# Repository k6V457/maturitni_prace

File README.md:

WOIP
completely incomplete repository

GOALS:
- [x] Create this repository
- [ ] Create graduation thesis
  - [ ] Create template in $\LaTeX$
  - [ ] fill in blank spaces
  - [ ] modify template for SPSKA purposes
  - [ ] Write INTRO and theoretical part
  - [ ] start working on practical part

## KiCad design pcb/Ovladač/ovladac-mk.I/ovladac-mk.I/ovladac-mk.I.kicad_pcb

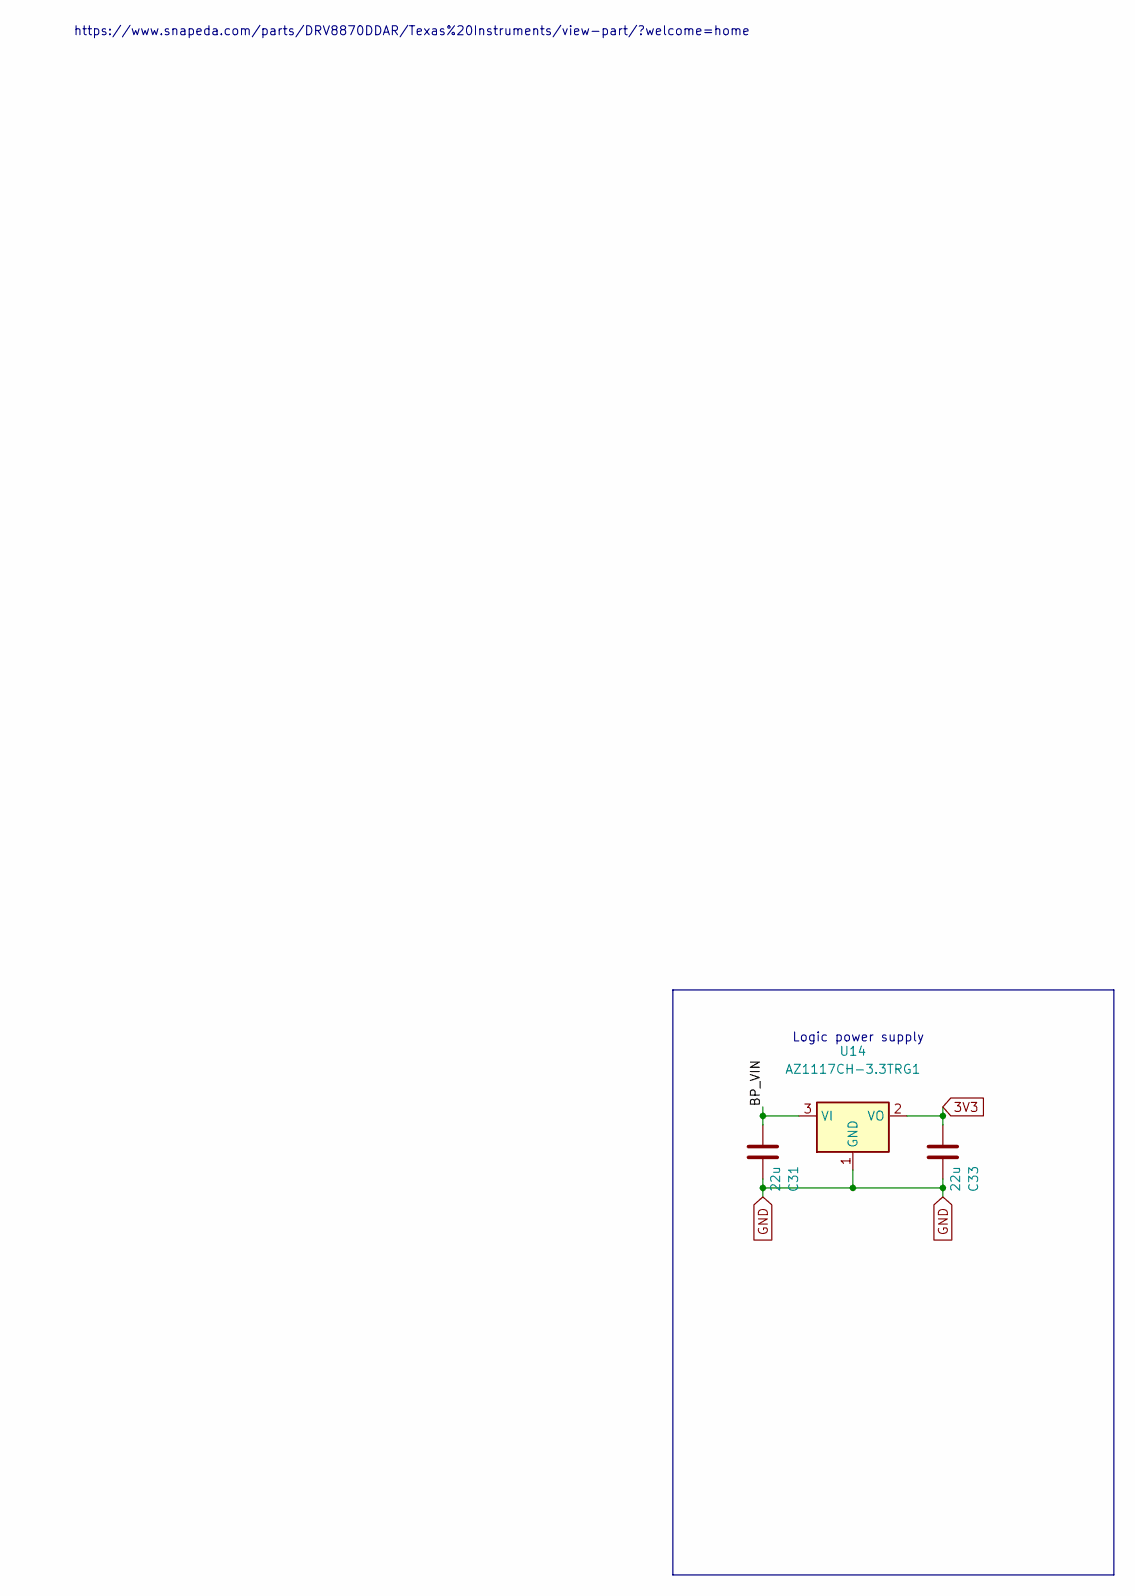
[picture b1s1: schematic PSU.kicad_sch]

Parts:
C31, C33: 22u; C_0603_1608Metric
U14: AZ1117CH-3.3TRG1; SOT-223-3_TabPin2

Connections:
3V3: C33.2, U14.2 (VO); also elsewhere on the board
/PSU/BP_VIN: C31.2, U14.3 (VI); also elsewhere on the board
GND: C31.1, C33.1, U14.1 (GND); also elsewhere on the board

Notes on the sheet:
Logic power supply
https://www.snapeda.com/parts/DRV8870DDAR/Texas%20Instruments/view-part/?welcome=home

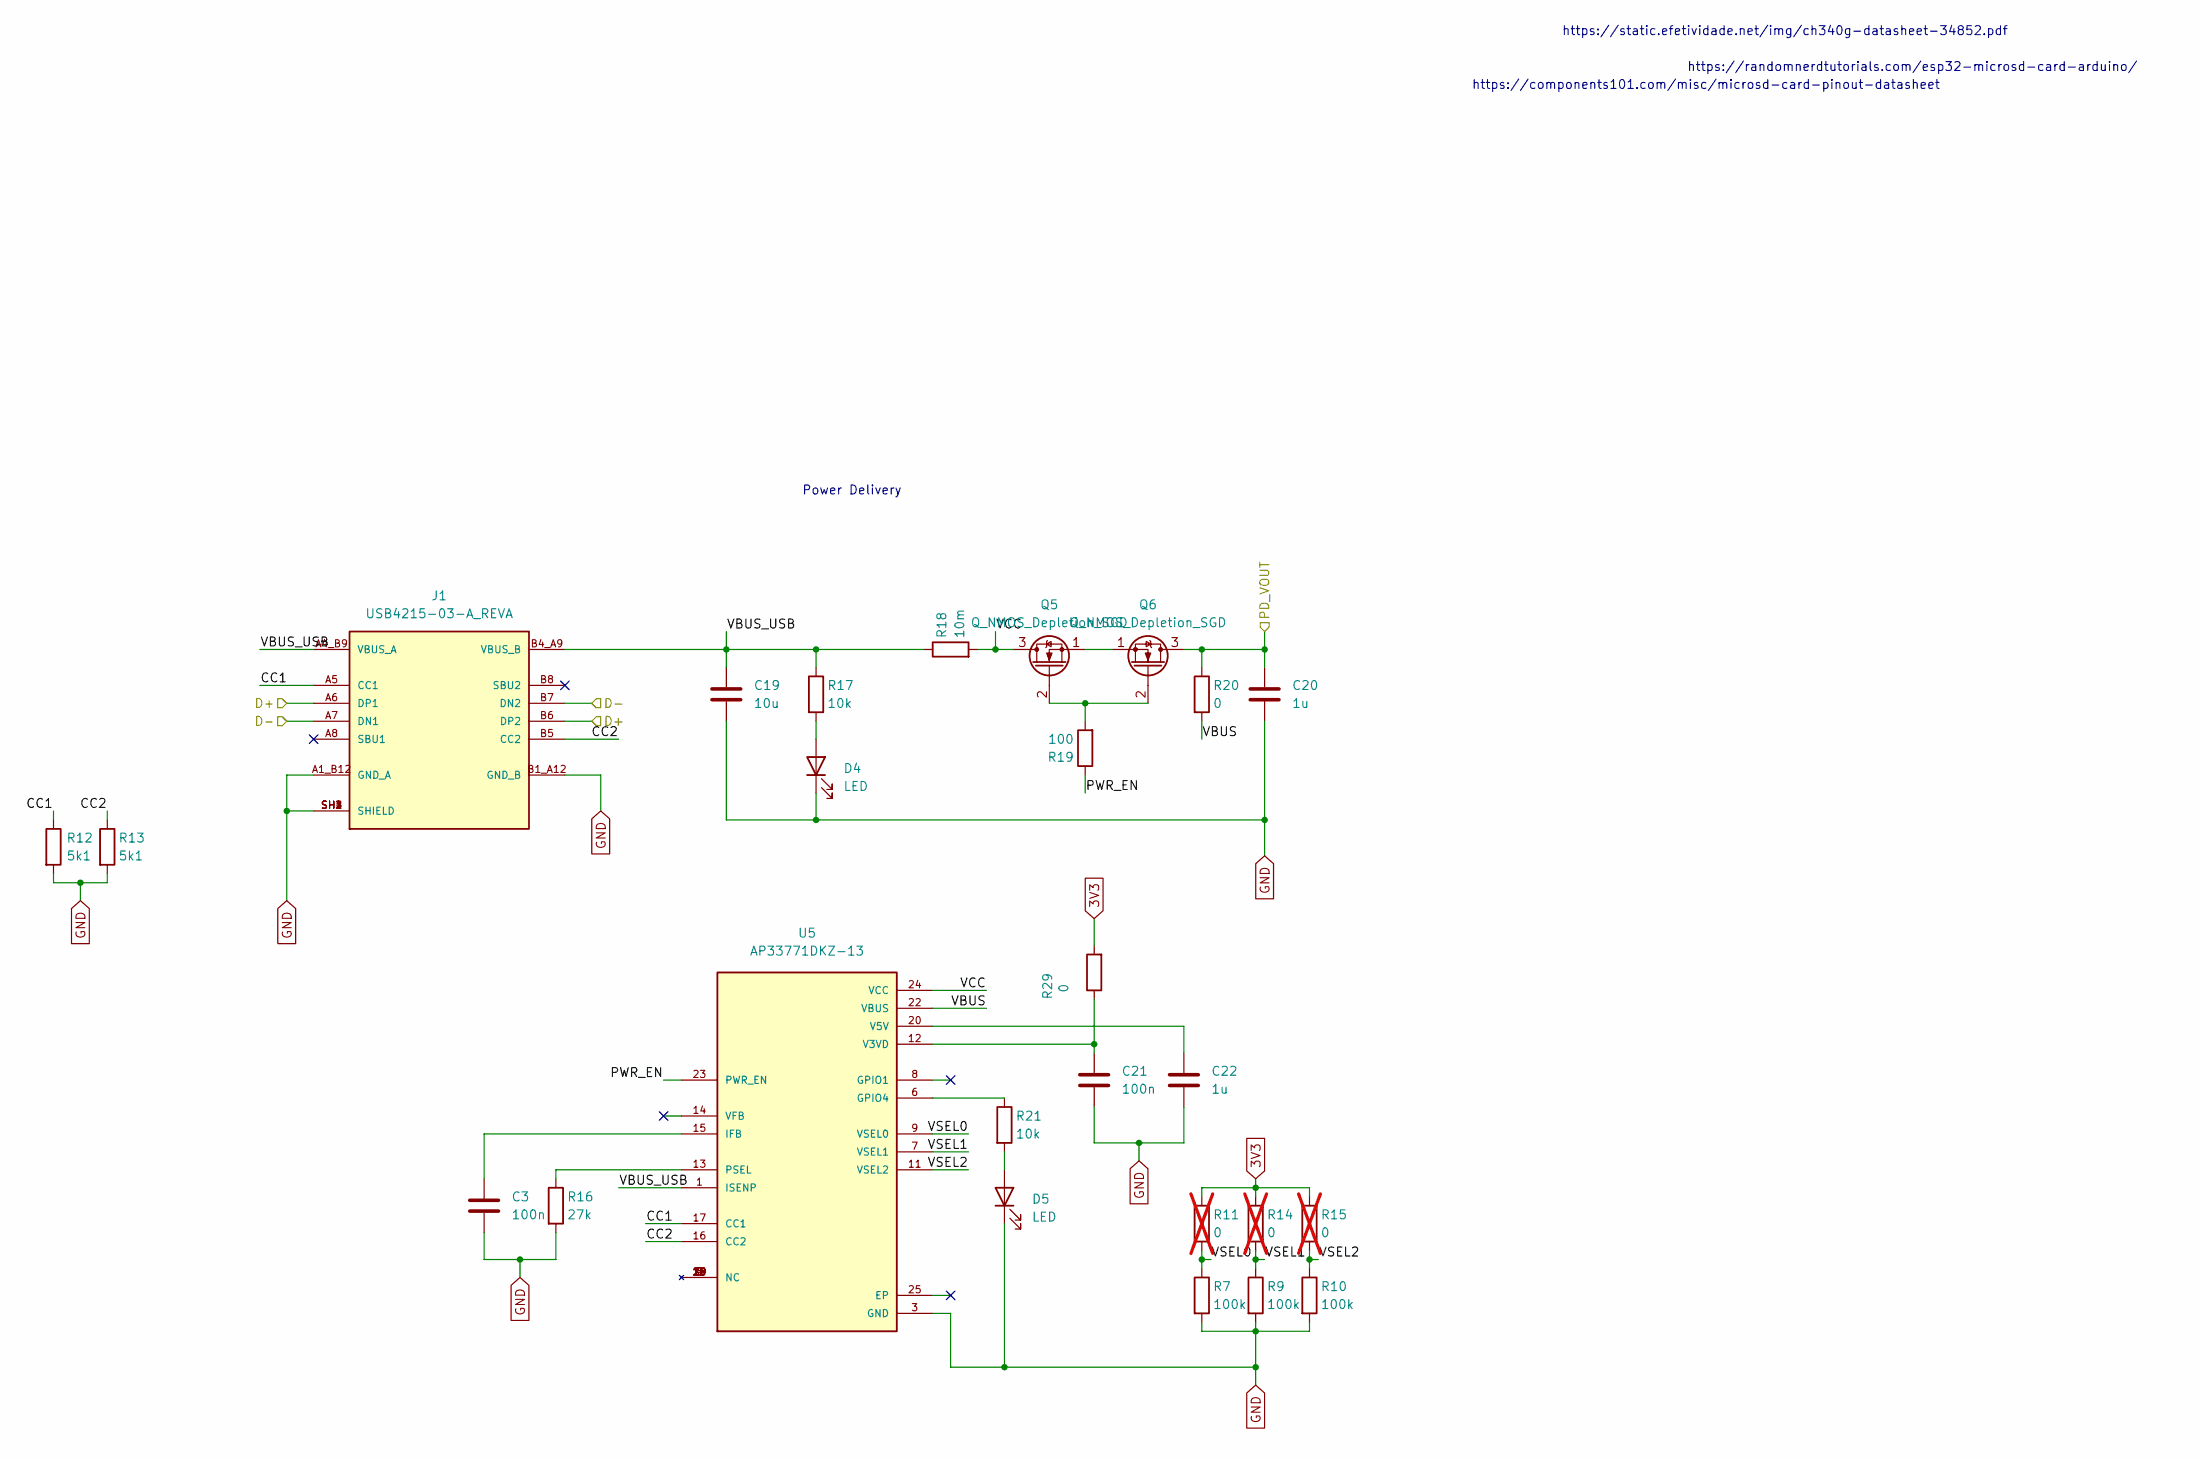
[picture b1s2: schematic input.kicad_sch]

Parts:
C3, C21: 100n; C_0201_0603Metric
C19: 10u; C_0201_0603Metric
C20, C22: 1u; C_0201_0603Metric
D4, D5: LED; LED_0805_2012Metric_Pad1.15x1.40mm_HandSolder
J1: USB4215-03-A_REVA; GCT_USB4215-03-A_REVA; PARTREV A
Q5, Q6: Q_NMOS_Depletion_SGD; SOT-23
R7, R9, R10: 100k; R_0201_0603Metric
R11, R14, R15: 0; R_0201_0603Metric; not fitted
R12, R13: 5k1; R_0201_0603Metric
R16: 27k; R_0805_2012Metric_Pad1.20x1.40mm_HandSolder
R17, R21: 10k; R_0201_0603Metric
R18: 10m; R_0603_1608Metric
R19: 100; R_0201_0603Metric
R20, R29: 0; R_0201_0603Metric
U5: AP33771DKZ-13; IC_AP33771DKZ-13; PARTREV 5-2; DigiKey_Part_Number 31-AP33771DKZ-13TR-ND

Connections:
3V3: R11.1, R14.1, R15.1, R29.2; also elsewhere on the board
/ESP32/IO19: J1.A7 (DN1), J1.B7 (DN2); also elsewhere on the board
/ESP32/IO20: J1.A6 (DP1), J1.B6 (DP2); also elsewhere on the board
/Input/CC1: J1.A5 (CC1), R12.1, U5.17 (CC1)
/Input/CC2: J1.B5 (CC2), R13.1, U5.16 (CC2)
/Input/PD_VOUT: C20.1, Q6.3 (D), R20.1
/Input/PWR_EN: R19.1, U5.23 (PWR_EN)
/Input/VBUS: R20.2, U5.22 (VBUS)
/Input/VBUS_USB: C19.1, J1.A4_B9 (VBUS_A), J1.B4_A9 (VBUS_B), R17.1, R18.1, U5.1 (ISENP)
/Input/VCC: Q5.3 (D), R18.2, U5.24 (VCC)
/Input/VSEL0: R7.1, R11.2, U5.9 (VSEL0)
/Input/VSEL1: R9.1, R14.2, U5.7 (VSEL1)
/Input/VSEL2: R10.1, R15.2, U5.11 (VSEL2)
GND: C3.2, C19.2, C20.2, C21.2, C22.2, D4.1 (K), D5.1 (K), J1.A1_B12 (GND_A), J1.B1_A12 (GND_B), J1.SH1 (SHIELD), J1.SH2 (SHIELD), J1.SH3 (SHIELD), J1.SH4 (SHIELD), R7.2, R9.2, R10.2, R12.2, R13.2, R16.2, U5.3 (GND); also elsewhere on the board
unnamed: D4.2 (A), R17.2
unnamed: D5.2 (A), R21.2
unnamed: Q5.2 (G), Q6.2 (G), R19.2
unnamed: Q5.1 (S), Q6.1 (S)
unnamed: R21.1, U5.6 (GPIO4)
unnamed: C3.1, U5.15 (IFB)
unnamed: R16.1, U5.13 (PSEL)
unnamed: C21.1, R29.1, U5.12 (V3VD)
unnamed: C22.1, U5.20 (V5V)

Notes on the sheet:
https://components101.com/misc/microsd-card-pinout-datasheet
https://static.efetividade.net/img/ch340g-datasheet-34852.pdf
https://randomnerdtutorials.com/esp32-microsd-card-arduino/
Power Delivery

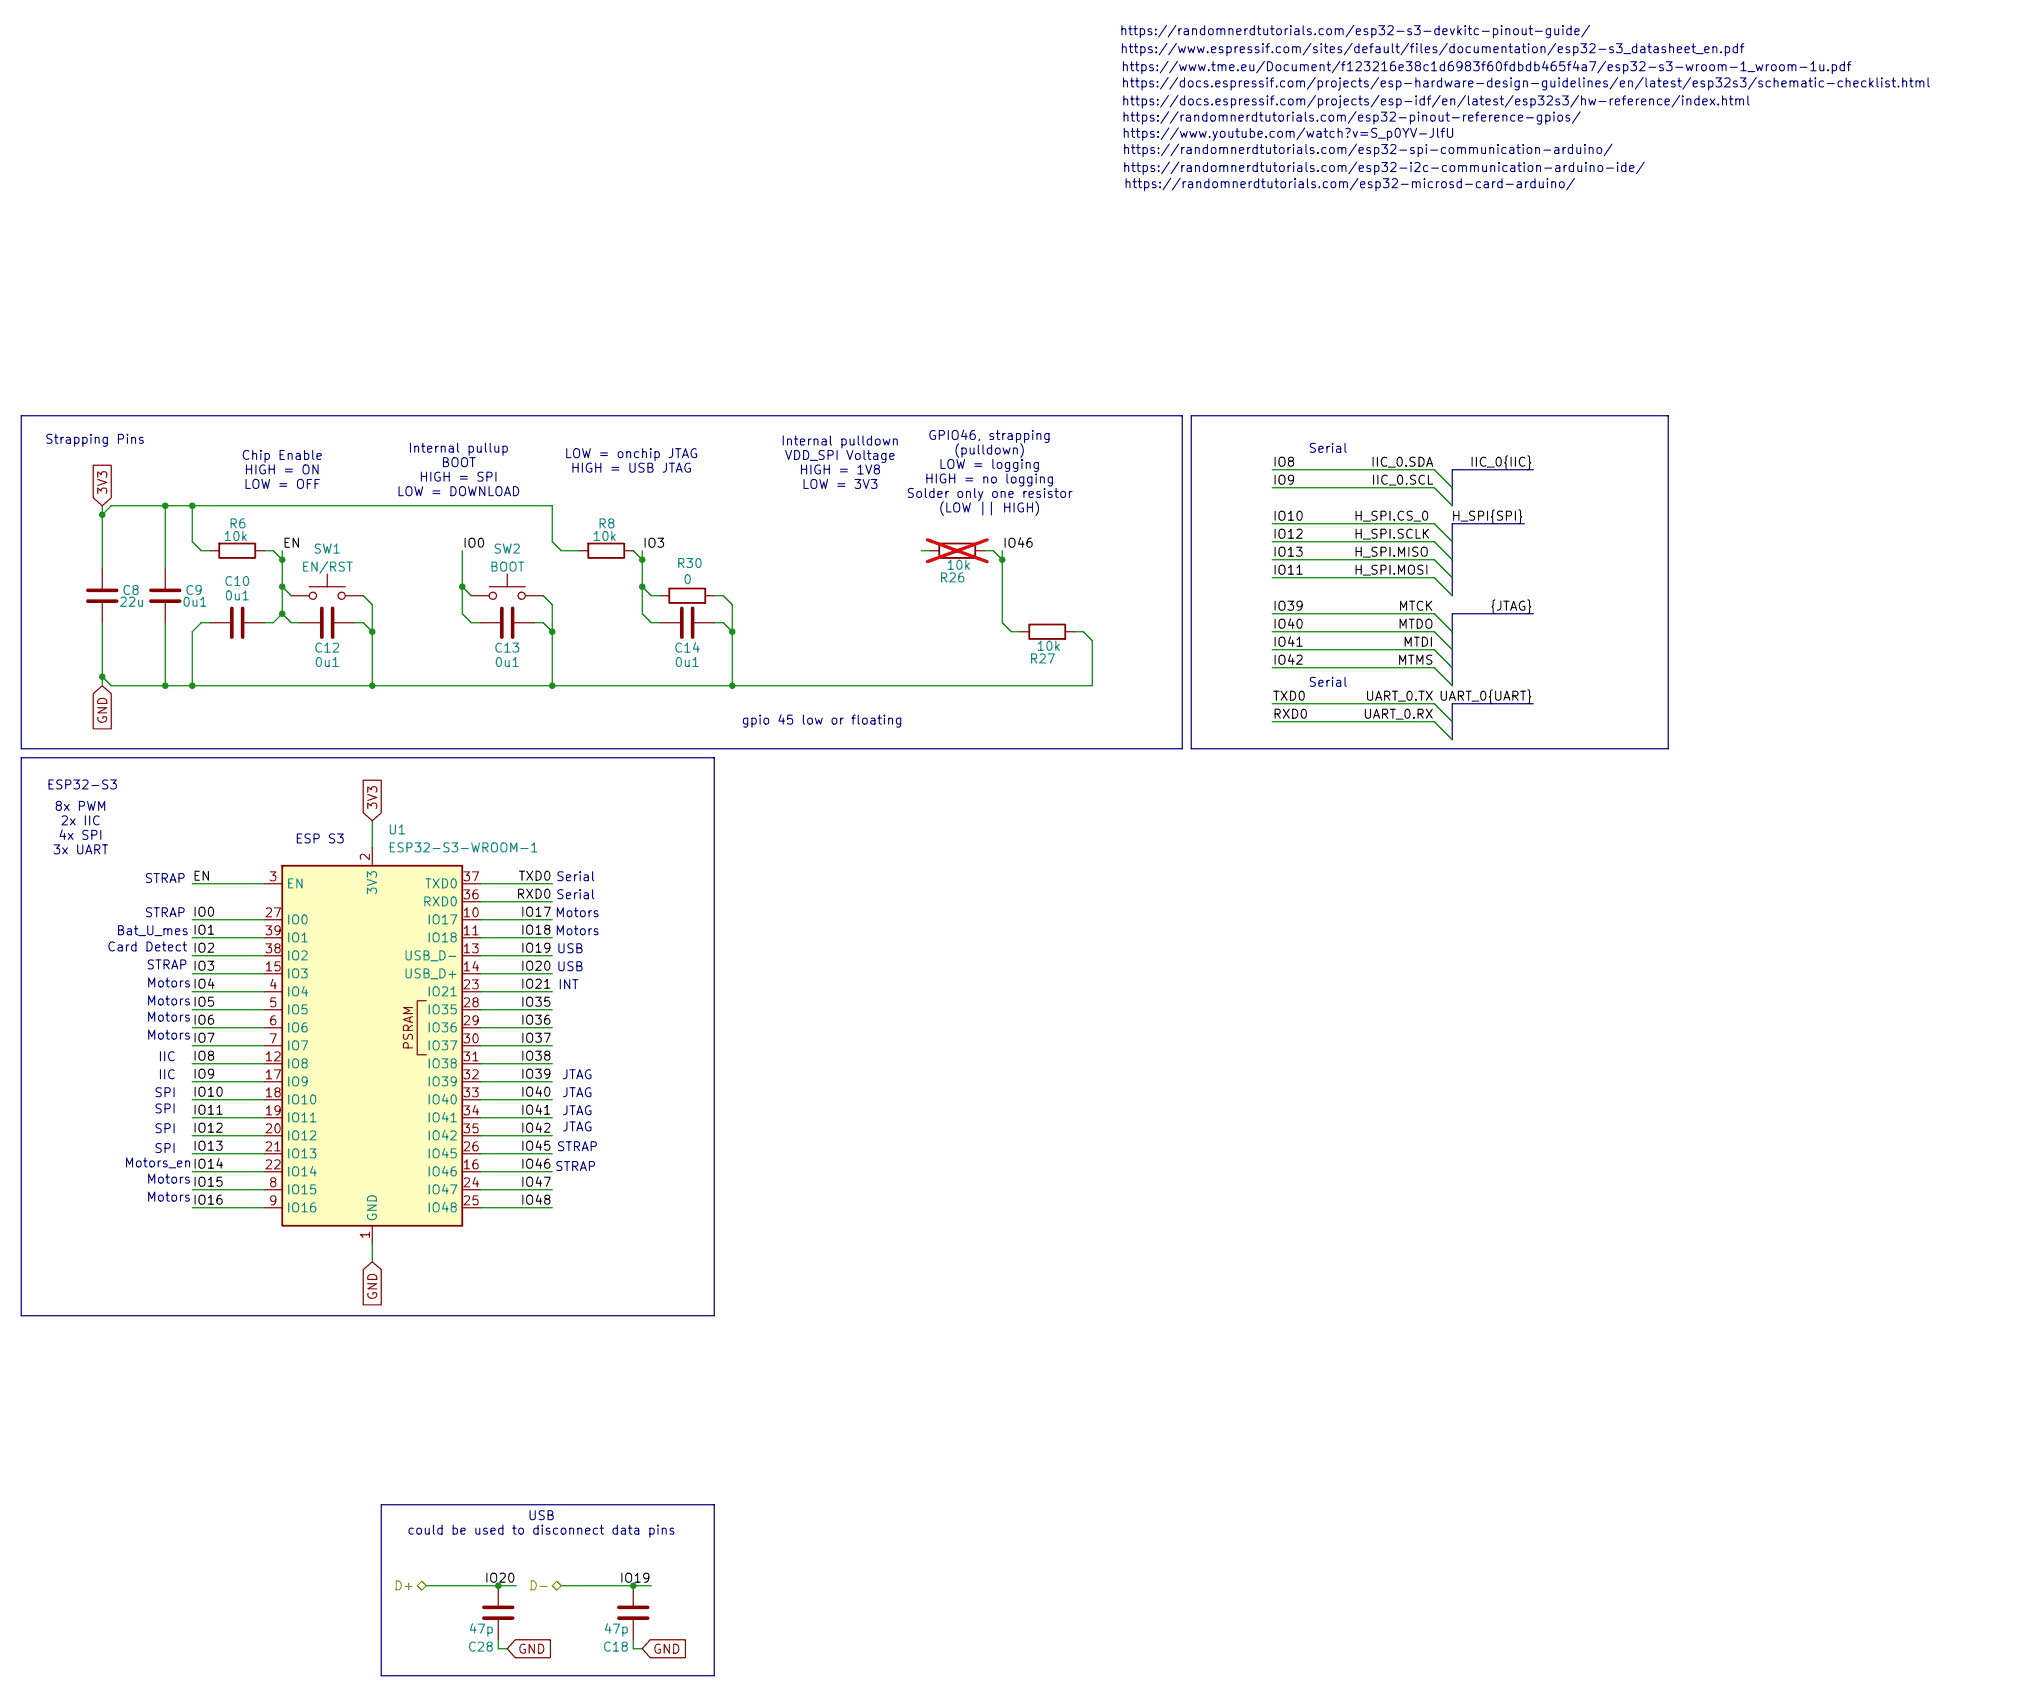
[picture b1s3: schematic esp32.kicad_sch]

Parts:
C8: 22u; C_0402_1005Metric
C9: 0u1; C_0402_1005Metric
C10, C12, C13, C14: 0u1; C_0201_0603Metric
C18, C28: 47p; C_0201_0603Metric
R6, R8, R27: 10k; R_0201_0603Metric
R26: 10k; R_0201_0603Metric; not fitted
R30: 0; R_0201_0603Metric
SW1: EN/RST; SW_TL3305AF160QG
SW2: BOOT; SW_TL3305AF160QG
U1: ESP32-S3-WROOM-1

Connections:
3V3: C8.1, C9.1, R6.2, R8.2, U1.2 (3V3); also elsewhere on the board
/ESP32/EN: C10.1, C12.2, R6.1, SW1.1, U1.3 (EN)
/ESP32/H_SPI.CS_0: U1.18 (IO10)
/ESP32/H_SPI.MISO: U1.21 (IO13)
/ESP32/H_SPI.MOSI: U1.19 (IO11)
/ESP32/H_SPI.SCLK: U1.20 (IO12)
/ESP32/IIC_0.SCL: U1.17 (IO9)
/ESP32/IIC_0.SDA: U1.12 (IO8)
/ESP32/IO0: C13.1, SW2.2, U1.27 (IO0)
/ESP32/IO1: U1.39 (IO1)
/ESP32/IO2: U1.38 (IO2)
/ESP32/IO3: C14.1, R8.1, R30.1, U1.15 (IO3)
/ESP32/IO4: U1.4 (IO4)
/ESP32/IO5: U1.5 (IO5)
/ESP32/IO6: U1.6 (IO6)
/ESP32/IO7: U1.7 (IO7)
/ESP32/IO14: U1.22 (IO14)
/ESP32/IO15: U1.8 (IO15)
/ESP32/IO16: U1.9 (IO16)
/ESP32/IO17: U1.10 (IO17)
/ESP32/IO18: U1.11 (IO18)
/ESP32/IO19: C18.2, U1.13 (USB_D-); also elsewhere on the board
/ESP32/IO20: C28.2, U1.14 (USB_D+); also elsewhere on the board
/ESP32/IO21: U1.23 (IO21)
/ESP32/IO35: U1.28 (IO35)
/ESP32/IO36: U1.29 (IO36)
/ESP32/IO37: U1.30 (IO37)
/ESP32/IO38: U1.31 (IO38)
/ESP32/IO39: U1.32 (IO39)
/ESP32/IO40: U1.33 (IO40)
/ESP32/IO41: U1.34 (IO41)
/ESP32/IO42: U1.35 (IO42)
/ESP32/IO45: U1.26 (IO45); also elsewhere on the board
/ESP32/IO46: R26.2, R27.1, U1.16 (IO46)
/ESP32/IO47: U1.24 (IO47)
/ESP32/IO48: U1.25 (IO48)
/ESP32/RXD0: U1.36 (RXD0)
/ESP32/TXD0: U1.37 (TXD0)
GND: C8.2, C9.2, C10.2, C12.1, C13.2, C14.2, C18.1, C28.1, R27.2, R30.2, SW1.2, SW2.1, U1.1 (GND), U1.40 (GND), U1.41 (GND); also elsewhere on the board

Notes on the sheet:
Motors
8x PWM 2x IIC 4x SPI 3x UART
STRAP
LOW = onchip JTAG HIGH = USB JTAG
https://docs.espressif.com/projects/esp-hardware-design-guidelines/en/latest/esp32s3/schematic-checklist.html
Bat_U_mes
Serial
SPI
https://www.youtube.com/watch?v=S_p0YV-JlfU
ESP32-S3
SPI
JTAG
https://randomnerdtutorials.com/esp32-s3-devkitc-pinout-guide/
USB
https://www.tme.eu/Document/f123216e38c1d6983f60fdbdb465f4a7/esp32-s3-wroom-1_wroom-1u.pdf
ESP S3
USB could be used to disconnect data pins
Card Detect
https://randomnerdtutorials.com/esp32-spi-communication-arduino/
gpio 45 low or floating
Serial
Strapping Pins
Internal pulldown VDD_SPI Voltage HIGH = 1V8 LOW = 3V3
Chip Enable HIGH = ON LOW = OFF
Internal pullup BOOT HIGH = SPI LOW = DOWNLOAD
GPIO46, strapping (pulldown) LOW = logging HIGH = no logging Solder only one resistor (LOW || HIGH)
Motors_en
https://randomnerdtutorials.com/esp32-microsd-card-arduino/
https://www.espressif.com/sites/default/files/documentation/esp32-s3_datasheet_en.pdf
https://docs.espressif.com/projects/esp-idf/en/latest/esp32s3/hw-reference/index.html
IIC
https://randomnerdtutorials.com/esp32-pinout-reference-gpios/
https://randomnerdtutorials.com/esp32-i2c-communication-arduino-ide/
INT
JTAG

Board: 2 copper layers, 49 parts (0 on the bottom side), 30 nets, no tracks yet.

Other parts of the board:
C34, C35: 22u; C_0603_1608Metric
R28: 10k; R_0201_0603Metric
U13: AZ1117CH-5.0TRG1; SOT-223-3_TabPin2

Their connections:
5V: C35.2, U13.2 (VO)
/ESP32/IO45: R28.1; also elsewhere on the board
/PSU/BP_VIN: C34.2, U13.3 (VI); also elsewhere on the board
GND: C34.1, C35.1, R28.2, U13.1 (GND); also elsewhere on the board

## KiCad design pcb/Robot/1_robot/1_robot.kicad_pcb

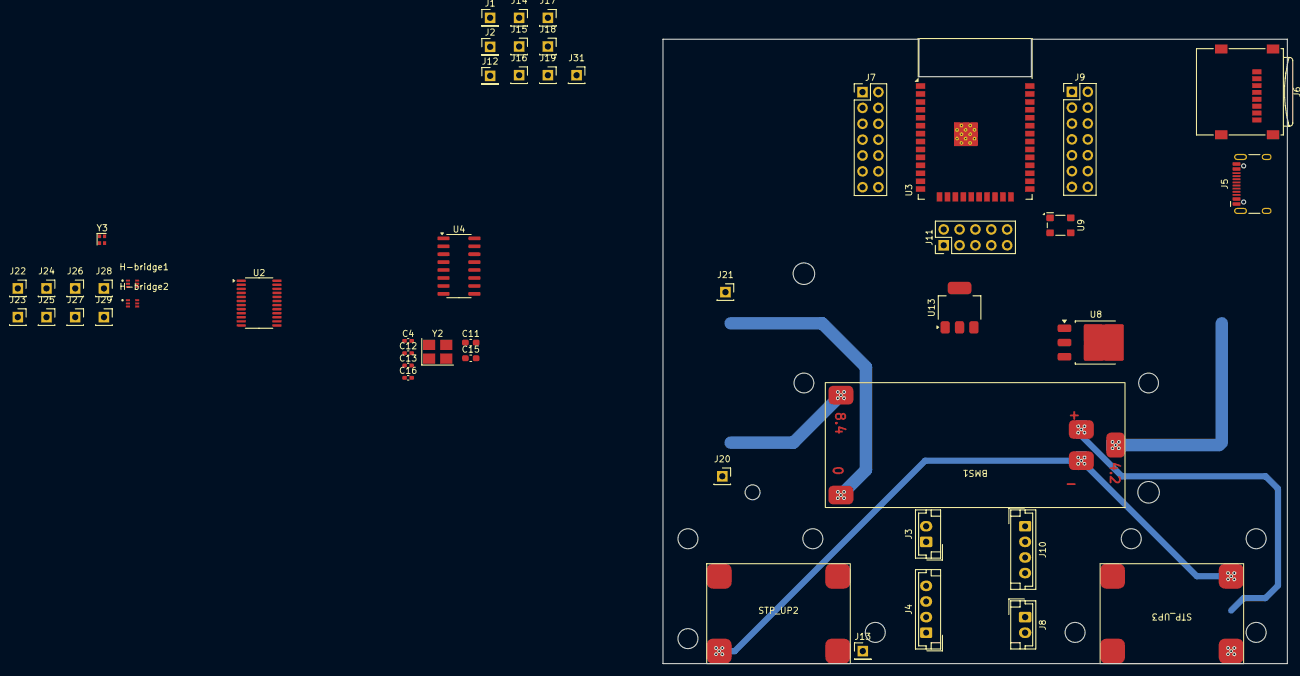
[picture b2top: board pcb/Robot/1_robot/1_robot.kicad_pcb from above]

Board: 2 copper layers, 100.0 x 100.0 mm, 50 parts (1 on the bottom side), 47 nets.

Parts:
BMS1: 2S 20A; BMS
BT1: 1048P; BAT_1048P
C4, C12, C13, C16: C; C_0402_1005Metric_Pad0.74x0.62mm_HandSolder
C11, C15: C; C_0603_1608Metric_Pad1.08x0.95mm_HandSolder
H-bridge1, H-bridge2: SOT50P160X60-6N
J1, J2, J12, J13: Conn_01x01_Socket; PinHeader_1x01_P2.54mm_Vertical
J3, J8: Conn_01x02_Pin; JST_EH_B2B-EH-A_1x02_P2.50mm_Vertical
J4, J10: Conn_01x04_Pin; JST_EH_B4B-EH-A_1x04_P2.50mm_Vertical
J5: USB_C_Receptacle_USB2.0_16P; USB_C_Receptacle_HCTL_HC-TYPE-C-16P-01A
J6: Micro_SD_Card_Det1; microSD_HC_Wuerth_693072010801
J7, J9: Conn_01x14_Pin; PinHeader_2x07_P2.54mm_Vertical
J11: Conn_01x10_Pin; PinHeader_2x05_P2.54mm_Vertical
J14, J15, J16, J17, J18, J19, J20, J21, J22, J23, J24, J25, J26, J27, J28, J29, J31: Conn_01x01_Socket; PinSocket_1x01_P2.54mm_Vertical
STP_UP2, STP_UP3: H-bridge_SX1308 2A
U2: TCA9548APWR; TSSOP-24_4.4x7.8mm_P0.65mm
U3: ESP32-WROOM-32E; ESP32-WROOM-32D
U4: CH340G; SOIC-16_3.9x9.9mm_P1.27mm
U8: LD39150DT33; TO-252-3_TabPin2
U9: GP2S700HCP; Sharp_GP2S700HCP
U13: LD1117S50TR_SOT223; SOT-223-3_TabPin2
Y2: Crystal_GND24; Oscillator_SMD_Abracon_ASE-4Pin_3.2x2.5mm_HandSoldering
Y3: Crystal; Oscillator_SMD_Abracon_ASCO-4Pin_1.6x1.2mm

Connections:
3V3: C11.1, C12.1, C15.1, C16.1, J3.2, J6.4 (VDD), J7.2, J8.2, J15.1, U2.24 (VCC), U3.2 (VDD), U4.4 (V3), U4.16 (VCC), U8.3 (VO)
/5V: J16.1, U13.2 (VO)
/CS_1: J6.2 (DAT3/CD), J9.10, U3.29 (IO5)
/ESP32/EN: J7.3, U3.3 (EN)
/ESP32/IO0: J9.14, U3.25 (IO0)
/ESP32/IO2: J11.10, U3.24 (IO2)
/ESP32/IO4: J9.13, U3.26 (IO4), U9.4 (A)
/ESP32/IO12: J7.14, U3.14 (IO12)
/ESP32/IO13: J11.2, U3.16 (IO13)
/ESP32/IO14: J7.13, U3.13 (IO14)
/ESP32/IO15: J11.9, U3.23 (IO15)
/ESP32/IO16: J9.12, U3.27 (IO16)
/ESP32/IO17: J9.11, U3.28 (IO17)
/ESP32/IO25: J7.10, J10.1, J28.1, U3.10 (IO25)
/ESP32/IO26: J4.1, J7.11, J26.1, U3.11 (IO26)
/ESP32/IO27: J7.12, J10.2, J29.1, U3.12 (IO27)
/ESP32/IO32: J7.8, U3.8 (IO32), Y3.2
/ESP32/IO33: J7.9, U3.9 (IO33), Y3.1
/ESP32/IO34: J4.2, J7.6, J27.1, U3.6 (IO34)
/ESP32/IO35: J7.7, U3.7 (IO35)
/ESP32/RXD0: J9.5, U3.34 (RXD0/IO3)
/ESP32/SDI: J9.3, U3.36 (IO22)
/ESP32/SDO: J9.6, U3.33 (IO21)
/ESP32/Sensor_VN: J7.5, U3.5 (SENSOR_VN)
/ESP32/Sensor_VP: J7.4, U3.4 (SENSOR_VP)
/ESP32/TXD0: J9.4, U3.35 (TXD0/IO1)
/GND: BMS1.5 (OUT_GND), C4.2, C11.2, C12.2, C13.2, C15.2, C16.2, J4.3, J5.A1 (GND), J5.A12 (GND), J5.B1 (GND), J5.B12 (GND), J5.S1 (SHIELD), J6.6 (VSS), J7.1, J9.1, J10.3, J11.1, J14.1, J17.1, J18.1, STP_UP2.2 (GND_IN), STP_UP3.2 (GND_IN), U2.12 (GND), U3.1 (GND), U3.15 (GND), U3.38 (GND), U3.39 (GND), U4.1 (GND), U8.2 (GND), U9.3 (K), U13.1 (GND), Y2.2, Y2.4
/H-Bridge/+12_1: J1.1, STP_UP3.3 (VOUT)
/H-Bridge/+12_2: J12.1, STP_UP2.3 (VOUT)
/H-Bridge/GND_12_1: J2.1, STP_UP3.4 (GND_OUT)
/H-Bridge/GND_12_2: J13.1, STP_UP2.4 (GND_OUT)
/Input/D+: J5.A6 (D+), J5.B6 (D+)
/Input/D-: J5.A7 (D-), J5.B7 (D-)
/Input/VBUS_USB: J5.A4 (VBUS), J5.A9 (VBUS), J5.B4 (VBUS), J5.B9 (VBUS)
/MISO: J6.7 (DAT0), J9.8, U3.31 (IO19)
/MOSI: J6.3 (CMD), J9.2, U3.37 (IO23)
/PSU/BP_VIN: BMS1.4 (OUT_8.4V), J19.1, U8.1 (VI), U9.2, U13.3 (VI)
/SCLK: J6.5 (CLK), J9.9, U3.30 (IO18)
unnamed: BMS1.3 (0V), BT1.N1, J21.1
unnamed: BMS1.2 (4.2V), BT1.N2, BT1.P1, J31.1
unnamed: BMS1.1 (8.4V), BT1.P2, J20.1
unnamed: J8.1, J22.1
unnamed: J10.4, J24.1
unnamed: J3.1, J23.1
unnamed: J4.4, J25.1
unnamed: C4.1, U4.7 (XI), Y2.1
unnamed: C13.1, U4.8 (XO), Y2.3

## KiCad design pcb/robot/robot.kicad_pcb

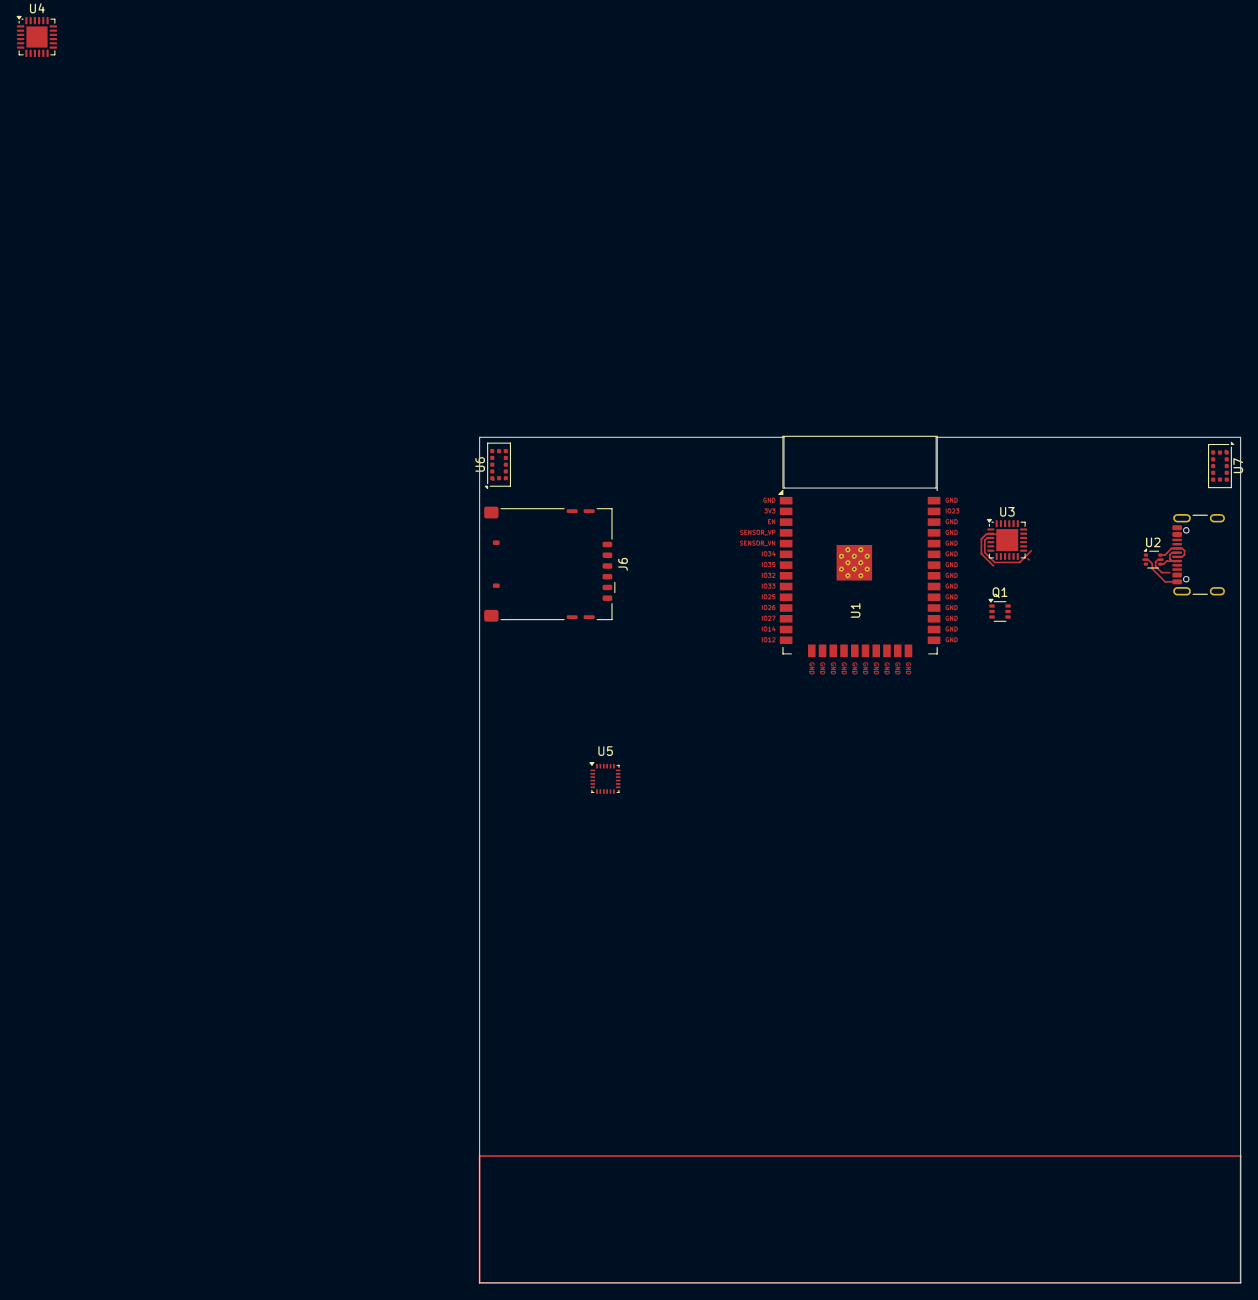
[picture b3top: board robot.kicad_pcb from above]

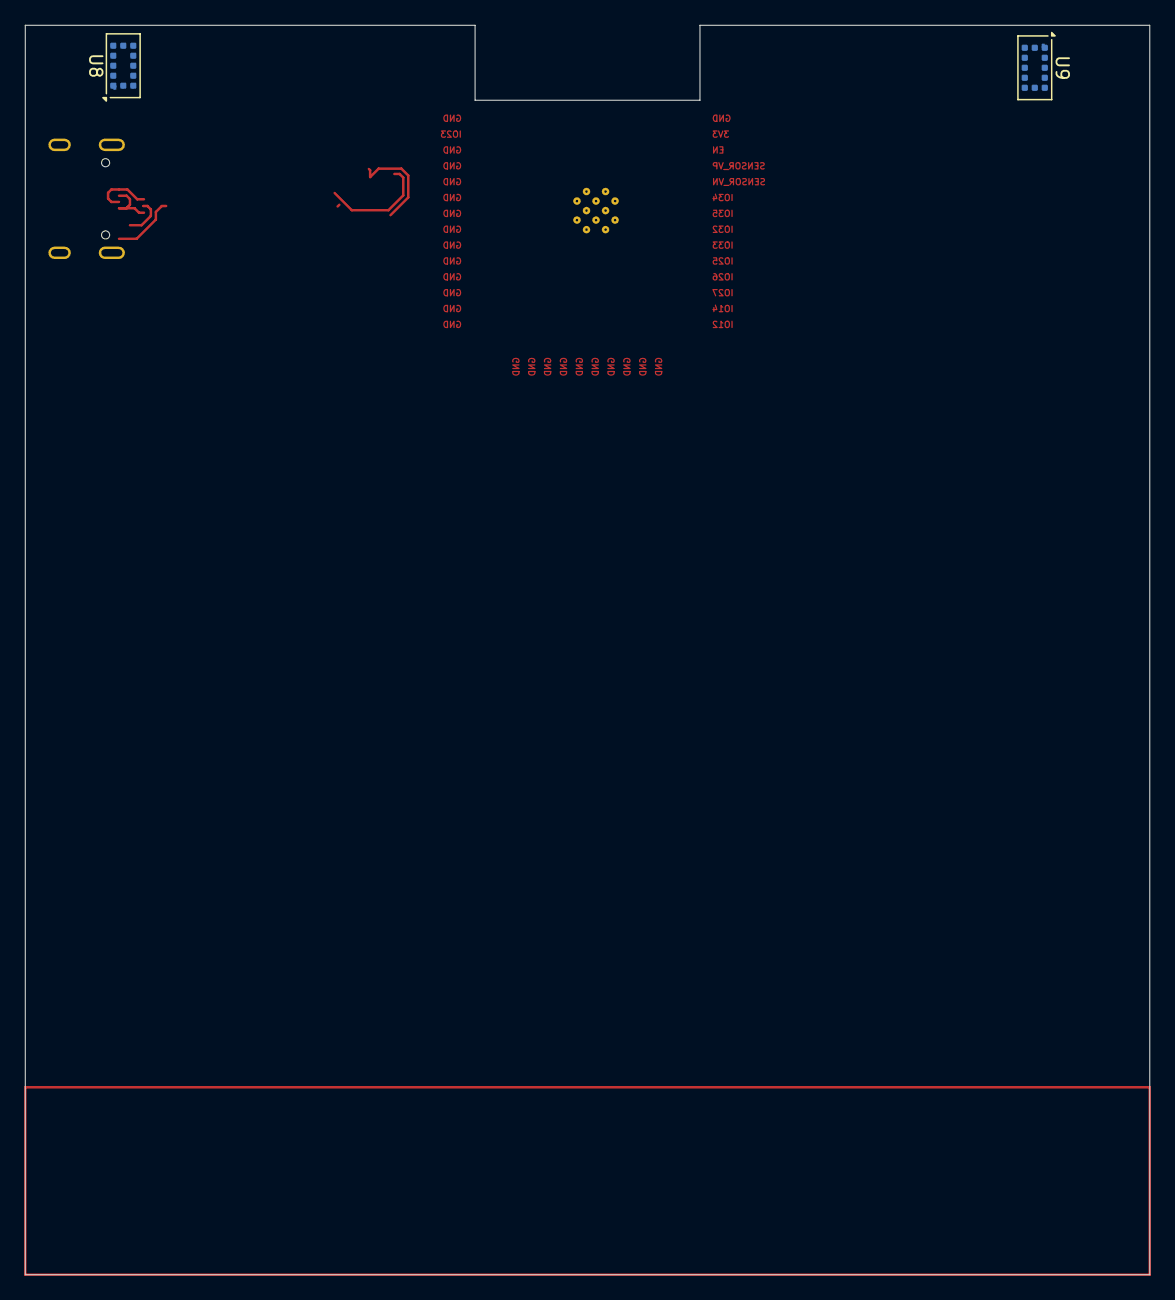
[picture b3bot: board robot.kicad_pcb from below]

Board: 2 copper layers, 90.0 x 100.0 mm, 12 parts (2 on the bottom side), 16 nets.

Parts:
J1: USB_C_Receptacle_USB2.0_16P; USB_C_Receptacle_GCT_USB4105-xx-A_16P_TopMnt_Horizontal
J6: Micro_SD_Card_Det1; microSIM_JAE_SF53S006VCBR2000
Q1: UMH3N; SOT-363_SC-70-6
U1: ESP32-WROOM-32
U2: USBLC6-2P6; SOT-666
U3: CP2104; QFN-24-1EP_4x4mm_P0.5mm_EP2.6x2.6mm
U4: BQ25887; VQFN-24-1EP_4x4mm_P0.5mm_EP2.5x2.5mm
U5: MPU-9250; InvenSense_QFN-24_3x3mm_P0.4mm
U6, U7, U8, U9: VL53L0CXV0DH1; ST_VL53L1x

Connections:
+5V: U2.5 (VBUS), U3.7 (REGIN), U3.8 (VBUS)
+5VP: J1.A4 (VBUS), J1.A9 (VBUS), J1.B4 (VBUS), J1.B9 (VBUS)
GND: J1.A1 (GND), J1.A12 (GND), J1.B1 (GND), J1.B12 (GND), J1.S1 (SHIELD), U1.1 (GND), U1.15 (GND), U1.38 (GND), U1.39 (GND), U2.2 (GND), U3.2 (GND), U3.25 (GND)
unnamed: J1.A6 (D+), J1.B6 (D+), U2.6 (I/O1)
unnamed: J1.A7 (D-), J1.B7 (D-), U2.4 (I/O2)
unnamed: U2.1 (I/O1), U3.3 (D+)
unnamed: U2.3 (I/O2), U3.4 (D-)
unnamed: U4.13 (BAT), U4.14 (BAT)
unnamed: U4.19 (GND), U4.20 (GND)
unnamed: U4.21 (PMID), U4.22 (PMID)
unnamed: U4.15 (SNS), U4.16 (SNS)
unnamed: U4.17 (SW), U4.18 (SW)
unnamed: U6.3 (GND), U6.4 (GND), U6.6 (GND), U6.12 (GND)
unnamed: U7.3 (GND), U7.4 (GND), U7.6 (GND), U7.12 (GND)
unnamed: U8.3 (GND), U8.4 (GND), U8.6 (GND), U8.12 (GND)
unnamed: U9.3 (GND), U9.4 (GND), U9.6 (GND), U9.12 (GND)
